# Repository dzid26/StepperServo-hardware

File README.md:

## StepperServoCAN Firmware
https://github.com/dzid26/StepperServoCAN

# StepperServo-hardware
Limits:
- 3.3A peak stall current per phase for 5sec
- 3.3A RMS combined motor continuous current for >1min (i.e. rotating under load but not stalled)
- 32V supply voltage

Features:
- Intended to drive a stepper motor
- High impedance freewheeling with overvoltage protection
- Magnetic angle sensor (can be turned off during sleep)
- CANbus transceiver with standby mode
- Debug port for flashing and configuration with ESD protection
- [Low-side](https://github.com/dzid26/StepperServoCAN/pull/38) current, V_mot and V_Bat, PCB temperature measurements
- Reverse polarity protection and swapped connectors protection; ESD protections on inputs

- Optional Enable port with [Break](https://github.com/dzid26/StepperServoCAN/pull/37) interrupt capability for additional safety
- Optional expansion port for connecting UART/I2C/PWM device or a sensor (0.4A max, or 1A for v0.6)
- Optional solder jumper pads, e.g. for motor identification

## Schematic

## PCB
- single sided PCB for direct mounting on the motor and efficient assembly
- flat bottom allows for heat dissipation and measuring motor temperature

## Motor
Motor tips:
- an examples of motor that produce a lot of torque without needing much gear ratio are Nema23 [104mm](https://www.omc-stepperonline.com/nema-23-bipolar-1-8deg-2-4nm-340oz-in-1-8a-4-95v-57x57x104mm-4-wires-23hs41-1804s) and [56mm](https://www.omc-stepperonline.com/nema-23-bipolar-1-8deg-1-16nm-164-3oz-in-1-5a-5-4v-57x57x56mm-4-wires-23hs22-1504s) - they have dense windings and high torque per amp values
- for space limited applications [this](https://www.aliexpress.com/item/4001349087963.html) coupled with single stage 5:1 gearbox can provide enough torque with relatively low friction and noise from the gearbox. Note: above 2Amps, the torque tapers off and torque ripple becomes apparent!
- rated current should not be exceeded by a lot to avoid torque ripple, motor inefficiency and overheating
- motors with high rated-current (less but thicker winding) can be used to avoid torque ripple problem, provided they are geared enough to generate enough output torque - however large gear ratios can be more prone to backlash and low efficiency which adds to backdrivinility friction
- generally big motors will have smoothest torque and don't need that much gearing

## Angle sensor magnet
- requires diametrically magnetized disk magnet
- Attaching magnet with the glue - [video](https://youtu.be/mQyXR3hITy0?t=41)
- Magnetic field [analysis](/Design/Magnet/README.md) 1-2mm thick and 5-6mm diameter magnets with about 1mm gap can be used

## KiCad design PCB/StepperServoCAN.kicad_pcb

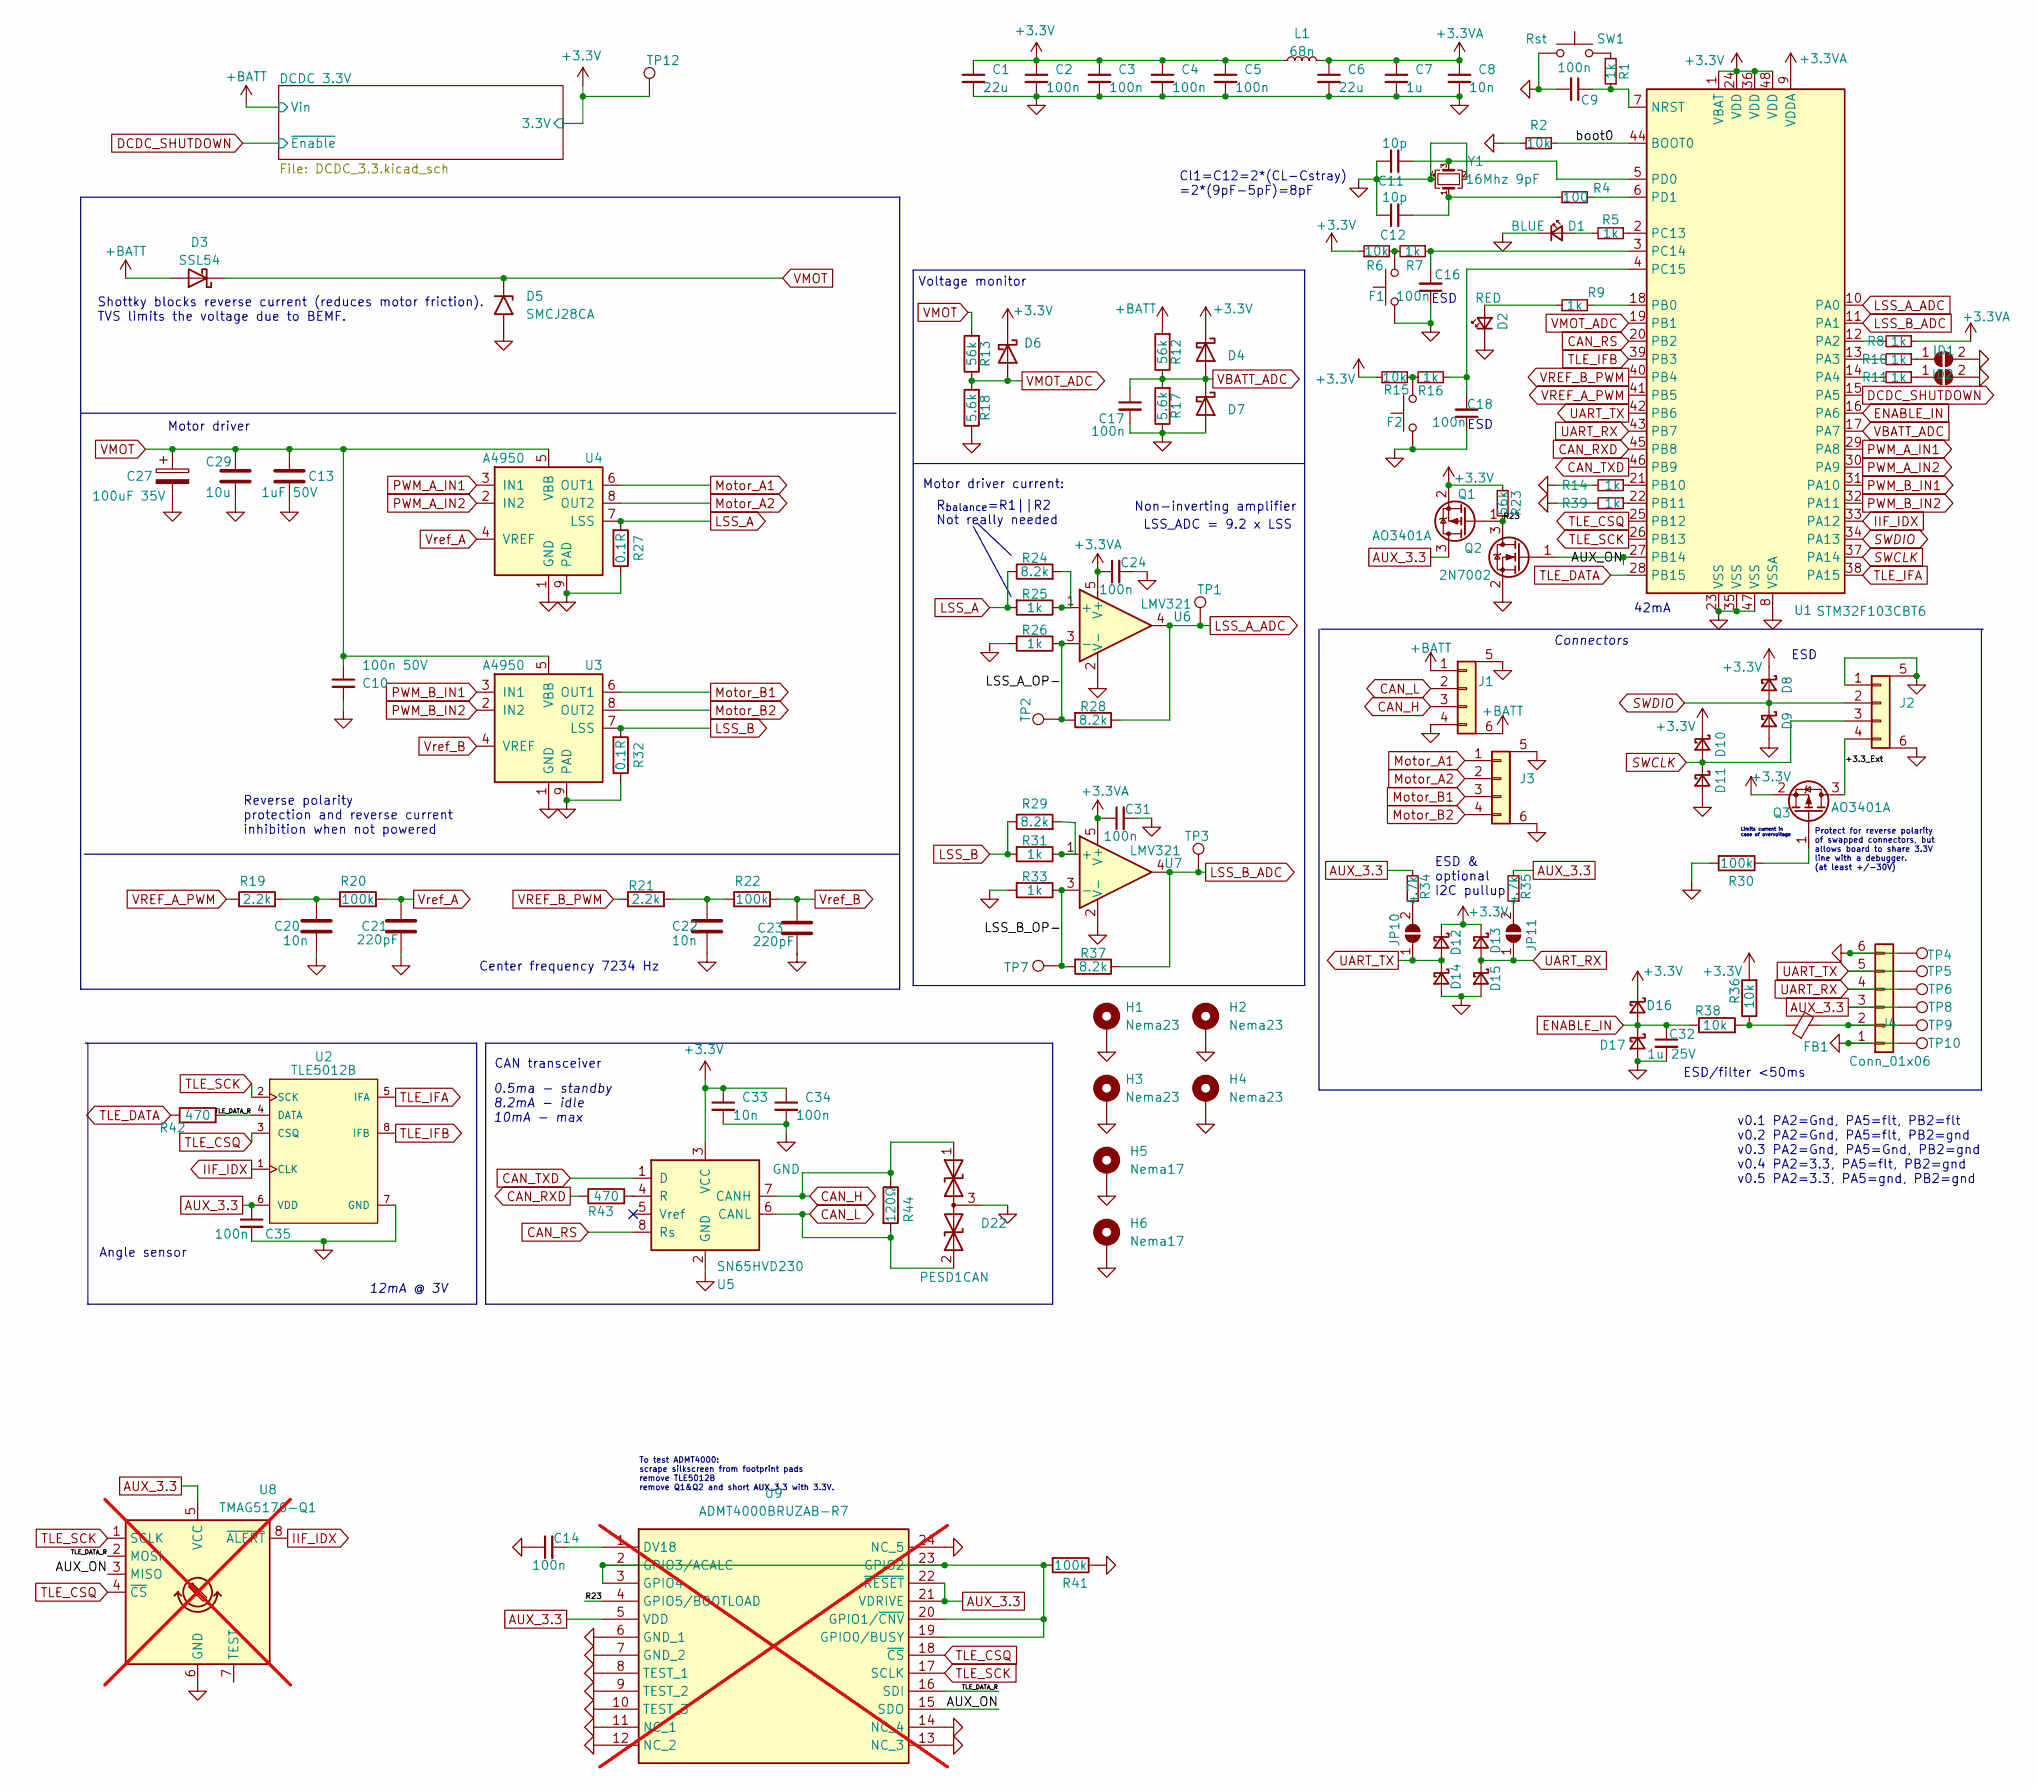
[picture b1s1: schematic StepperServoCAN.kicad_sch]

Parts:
C1, C6: 22u; C_0603_1608Metric; LCSC C59461
C2, C3, C4, C5, C9, C14, C16, C17, C18, C24, C31, C34, C35: 100n; C_0402_1005Metric; LCSC C1525
C7: 1u; C_0402_1005Metric; LCSC C52923
C8, C20, C22, C33: 10n; C_0402_1005Metric; LCSC C15195
C10: 100n 50V; C_0402_1005Metric; LCSC C307331
C11, C12: 10p; C_0402_1005Metric; LCSC C32949
C13: 1uF 50V; C_0805_2012Metric; LCSC C28323
C21, C23: 220pF; C_0402_1005Metric; LCSC C1530
C27: 100uF 35V; CP_Elec_6.3x5.7; LCSC C249982
C29: 10u; C_1206_3216Metric; LCSC C13585
C32: 1u 25V; C_0402_1005Metric; LCSC C52923
D1: BLUE; LED_0603_1608Metric; LCSC C2986058
D2: RED; LED_0603_1608Metric; LCSC C2286
D3: SSL54; D_SMB; LCSC C28646278
D4, D6, D7, D8, D9, D10, D11, D12, D13, D14, D15, D16, D17: 1N5819WS; D_SOD-323; LCSC C191023
D5: SMCJ28CA; D_SMC; LCSC C42371538
D22: PESD1CAN; SOT-23; LCSC C15771
F1, F2: Fcn>; SW_SPST_TL3342; LCSC C318884
FB1: FerriteBead 200mA; L_0603_1608Metric; LCSC C1002
H1, H2, H3, H4: Nema23; MountingHole_3.2mm_M3_ISO14580_Pad_TopOnly
H5, H6: Nema17; MountingHole_3.2mm_M3_ISO14580_Pad_TopOnly; LCSC C2928178
ID1, ID2: Jumper; SolderJumper-2_P1.3mm_Open_TrianglePad1.0x1.5mm
J1: CAR; JST-S4B-XH-SM4-TB; LCSC C54582908
J2: Debug; JST-S4B-XH-SM4-TB; LCSC C54582908
J3: Motor; JST-S4B-XH-SM4-TB; LCSC C54582908
J4: Conn_01x06; TerminalBlock_TE_282834-6_1x06_P2.54mm_Horizontal
JP10, JP11: I2C_PU; SolderJumper-2_P1.3mm_Open_RoundedPad1.0x1.5mm
L1: 68n; L_0603_1608Metric; LCSC C13415
Q1, Q3: AO3401A; SOT-23; LCSC C15127
Q2: 2N7002; SOT-23; LCSC C8545
R1, R5, R7, R8, R9, R10, R11, R14, R16, R25, R26, R31, R33, R39: 1k; R_0402_1005Metric; LCSC C11702
R2, R6, R15, R36, R38: 10k; R_0402_1005Metric; LCSC C25744
R4: 100; R_0402_1005Metric; LCSC C25076
R12, R13, R23: 56k; R_0402_1005Metric; LCSC C25796
R17, R18: 5.6k; R_0402_1005Metric; LCSC C25908
R19, R21: 2.2k; R_0402_1005Metric; LCSC C25879
R20, R22, R30, R41: 100k; R_0402_1005Metric; LCSC C25741
R24, R28, R29, R37: 8.2k; R_0402_1005Metric; LCSC C25924
R27, R32: 0.1R; R_1206_3216Metric_Pad1.30x1.75mm_HandSolder; LCSC C201308
R34, R35: 4.7k; R_0603_1608Metric_Pad0.98x0.95mm_HandSolder; LCSC C23162
R42, R43: 470; R_0603_1608Metric; LCSC C23179
R44: 120Ω; R_1206_3216Metric_Pad1.30x1.75mm_HandSolder; LCSC C17909
SW1: Rst; SW_SPST_TL3342; LCSC C318884
TP1, TP2, TP3, TP7: Pad; TestPoint_Pad_D1.0mm
TP4, TP5, TP6, TP8, TP9, TP10: WirePad; TestPoint_Pad_2.0x2.0mm
TP12: 3.3; TestPoint_Pad_D1.0mm
U1: STM32F103CBT6; LQFP-48_7x7mm_P0.5mm; LCSC C8734
U2: TLE5012B; Infineon-TLE5012-Level_A; LCSC C123083
U3, U4: A4950; SOIC-8-1EP_3.9x4.9mm_P1.27mm_EP2.41x3.3mm_ThermalVias; LCSC C82404
U5: SN65HVD230; SOIC-8_3.9x4.9mm_P1.27mm; LCSC C12084
U6, U7: LMV321; SOT-23-5; LCSC C7972
U8: TMAG5170-Q1; VSSOP-8_3x3mm_P0.65mm; LCSC C5220642; not fitted
U9: ADMT4000BRUZAB-R7; TSSOP-24_4.4x7.8mm_P0.65mm; not fitted
Y1: 16Mhz 9pF; Crystal_SMD_3225-4Pin_3.2x2.5mm; LCSC C13738

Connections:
+3.3V: C1.1, C2.1, C3.1, C4.1, C5.1, C33.1, C34.1, D4.1 (K), D6.1 (K), D8.1 (K), D10.1 (K), D12.1 (K), D13.1 (K), D16.1 (K), L1.1, Q1.2 (S), Q3.2 (S), R6.1, R15.1, R23.2, R36.2, TP12.1 (1_1), U1.1 (VBAT), U1.24 (VDD), U1.36 (VDD), U1.48 (VDD), U5.3 (VCC); also elsewhere on the board
+3.3VA: C6.1, C7.1, C8.1, C24.1, C31.1, L1.2, R8.1, U1.9 (VDDA), U6.5 (V+), U7.5 (V+)
+BATT: D3.2 (A), J1.1, J1.6 (Mount), R12.2; also elsewhere on the board
/+3.3_Ext: J2.4, Q3.3 (D)
/AUX_ON: Q2.1 (G), U1.27 (PB14), U8.3 (MISO), U9.15 (SDO)
/LSS_A_OP-: R26.1, R28.2, TP2.1 (1_1), U6.3 (-)
/LSS_B_OP-: R33.1, R37.2, TP7.1 (1_1), U7.3 (-)
/R23: Q1.1 (G), Q2.3 (D), R23.1, U9.4 (GPIO5/BOOTLOAD)
/TLE_DATA_R: R42.2, U2.4 (DATA), U8.2 (MOSI), U9.16 (SDI)
/boot0: R2.2, U1.44 (BOOT0)
AUX_3.3: C35.1, J4.3, Q1.3 (D), R34.2, R35.2, TP8.1 (1_1), U2.6 (VDD), U8.5 (VCC), U9.5 (VDD), U9.21 (VDRIVE), U9.22 (~RESET)
CAN_H: D22.1 (A1), J1.3, R44.1, U5.7 (CANH)
CAN_L: D22.2 (A2), J1.2, R44.2, U5.6 (CANL)
CAN_RS: U1.20 (PB2), U5.8 (Rs)
CAN_RXD: R43.1, U1.45 (PB8)
CAN_TXD: U1.46 (PB9), U5.1 (D)
DCDC_SHUTDOWN: U1.15 (PA5); also elsewhere on the board
ENABLE_IN: C32.1, D16.2 (A), D17.1 (K), R38.1, U1.16 (PA6)
GND: C1.2, C2.2, C3.2, C4.2, C5.2, C6.2, C7.2, C8.2, C9.2, C10.2, C11.1, C12.1, C13.2, C14.1, C16.1, C17.2, C18.1, C20.2, C21.2, C22.2, C23.2, C24.2, C27.2, C29.2, C31.2, C32.2, C33.2, C34.2, C35.2, D1.1 (K), D2.1 (K), D5.2 (A2), D7.2 (A), D9.2 (A), D11.2 (A), D14.2 (A), D15.2 (A), D17.2 (A), D22.3 (common), F1.2, F2.2, H1.1 (1_1), H2.1 (1_1), H3.1 (1_1), H4.1 (1_1), H5.1 (1_1), H6.1 (1_1), ID1.2 (B), ID2.2 (B), J1.4, J1.5 (Mount), J2.1, J2.5 (Mount), J2.6 (Mount), J3.5 (Mount), J3.6 (Mount), J4.1, J4.6, Q2.2 (S), R2.1, R14.2, R17.1, R18.1, R26.2, R27.1, R30.2, R32.1, R33.2, R39.2, R41.1, SW1.1, TP4.1 (1_1), TP10.1 (1_1), U1.8 (VSSA), U1.23 (VSS), U1.35 (VSS), U1.47 (VSS), U2.7 (GND), U3.1 (GND), U3.9 (PAD), U4.1 (GND), U4.9 (PAD), U5.2 (GND), U6.2 (V-), U7.2 (V-), U8.6 (GND), U9.6 (GND_1), U9.7 (GND_2), U9.8 (TEST_1), U9.9 (TEST_2), U9.10 (TEST_3), U9.11 (NC_1), U9.12 (NC_2), U9.13 (NC_3), U9.14 (NC_4), U9.24 (NC_5), Y1.2, Y1.4; also elsewhere on the board
IIF_IDX: U1.33 (PA12), U2.1 (CLK), U8.8 (~ALERT)
LSS_A: R24.1, R25.2, R27.2, U4.7 (LSS)
LSS_A_ADC: R28.1, TP1.1 (1_1), U1.10 (PA0), U6.4
LSS_B: R29.1, R31.2, R32.2, U3.7 (LSS)
LSS_B_ADC: R37.1, TP3.1 (1_1), U1.11 (PA1), U7.4
Motor_A1: J3.1, U4.6 (OUT1)
Motor_A2: J3.2, U4.8 (OUT2)
Motor_B1: J3.3, U3.6 (OUT1)
Motor_B2: J3.4, U3.8 (OUT2)
unnamed: C12.2, R4.1, Y1.1
unnamed: C20.1, R19.2, R20.1
unnamed: C22.1, R21.2, R22.1
unnamed: D1.2 (A), R5.2
unnamed: D2.2 (A), R9.1
unnamed: F1.1, R6.2, R7.2
unnamed: F2.1, R15.2, R16.1
unnamed: FB1.1, R36.1, R38.2
unnamed: ID1.1 (A), R10.1
unnamed: ID2.1 (A), R11.1
unnamed: FB1.2, J4.2, TP9.1 (1_1)
unnamed: JP10.2 (B), R34.1
unnamed: JP11.2 (B), R35.1
unnamed: Q3.1 (G), R30.1
unnamed: R1.2, SW1.2
unnamed: C9.1, R1.1, U1.7 (NRST)
unnamed: R8.2, U1.12 (PA2)
unnamed: R10.2, U1.13 (PA3)
unnamed: R11.2, U1.14 (PA4)
unnamed: R9.2, U1.18 (PB0)
unnamed: R14.1, U1.21 (PB10)
unnamed: R39.1, U1.22 (PB11)
unnamed: R5.1, U1.2 (PC13)
unnamed: C16.2, R7.1, U1.3 (PC14)
unnamed: C18.2, R16.2, U1.4 (PC15)
unnamed: C11.2, U1.5 (PD0), Y1.3
unnamed: R4.2, U1.6 (PD1)
unnamed: R43.2, U5.4 (R)
unnamed: R24.2, R25.1, U6.1 (+)
unnamed: R29.2, R31.1, U7.1 (+)
unnamed: C14.2, U9.1 (DV18)
unnamed: R41.2, U9.2 (GPIO3/ACALC), U9.3 (GPIO4), U9.19 (GPIO0/BUSY), U9.20 (GPIO1/~CNV), U9.23 (GPIO2)
PWM_A_IN1: U1.29 (PA8), U4.3 (IN1)
PWM_A_IN2: U1.30 (PA9), U4.2 (IN2)
PWM_B_IN1: U1.31 (PA10), U3.3 (IN1)
PWM_B_IN2: U1.32 (PA11), U3.2 (IN2)
SWCLK: D10.2 (A), D11.1 (K), J2.3, U1.37 (PA14)
SWDIO: D8.2 (A), D9.1 (K), J2.2, U1.34 (PA13)
TLE_CSQ: U1.25 (PB12), U2.3 (CSQ), U8.4 (~CS), U9.18 (~CS)
TLE_DATA: R42.1, U1.28 (PB15)
TLE_IFA: U1.38 (PA15), U2.5 (IFA)
TLE_IFB: U1.39 (PB3), U2.8 (IFB)
TLE_SCK: U1.26 (PB13), U2.2 (SCK), U8.1 (SCLK), U9.17 (SCLK)
UART_RX: D13.2 (A), D15.1 (K), J4.4, JP11.1 (A), TP6.1 (1_1), U1.43 (PB7)
UART_TX: D12.2 (A), D14.1 (K), J4.5, JP10.1 (A), TP5.1 (1_1), U1.42 (PB6)
VBATT_ADC: C17.1, D4.2 (A), D7.1 (K), R12.1, R17.2, U1.17 (PA7)
VMOT: C10.1, C13.1, C27.1, C29.1, D3.1 (K), D5.1 (A1), R13.2, U3.5 (VBB), U4.5 (VBB)
VMOT_ADC: D6.2 (A), R13.1, R18.2, U1.19 (PB1)
VREF_A_PWM: R19.1, U1.41 (PB5)
VREF_B_PWM: R21.1, U1.40 (PB4)
Vref_A: C21.1, R20.2, U4.4 (VREF)
Vref_B: C23.1, R22.2, U3.4 (VREF)

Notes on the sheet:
LSS_ADC = 9.2 x LSS
42mA
ESD & optional I2C pullup
R_{balance}=R1||R2 Not really needed
v0.1 PA2=Gnd, PA5=flt, PB2=flt v0.2 PA2=Gnd, PA5=flt, PB2=gnd v0.3 PA2=Gnd, PA5=Gnd, PB2=gnd v0.4 PA2=3.3, PA5=flt, PB2=gnd v0.5 PA2=3.3, PA5=gnd, PB2=gnd
CAN transceiver
Non-inverting amplifier
Center frequency 7234 Hz
Angle sensor
Protect for reverse polarity of swapped connectors, but allows board to share 3.3V line with a debugger. (at least +/-30V)
ESD
Motor driver
ESD/filter <50ms
Shottky blocks reverse current (reduces motor friction). TVS limits the voltage due to BEMF.
To test ADMT4000: scrape silkscreen from footprint pads remove TLE5012B remove Q1&Q2 and short AUX_3.3 with 3.3V.
Limits current in case of overvoltage
Connectors
12mA @ 3V
Reverse polarity protection and reverse current inhibition when not powered
Voltage monitor
0.5ma - standby 8.2mA - idle 10mA - max
Cl1=C12=2*(CL-Cstray) =2*(9pF-5pF)=8pF
Motor driver current:

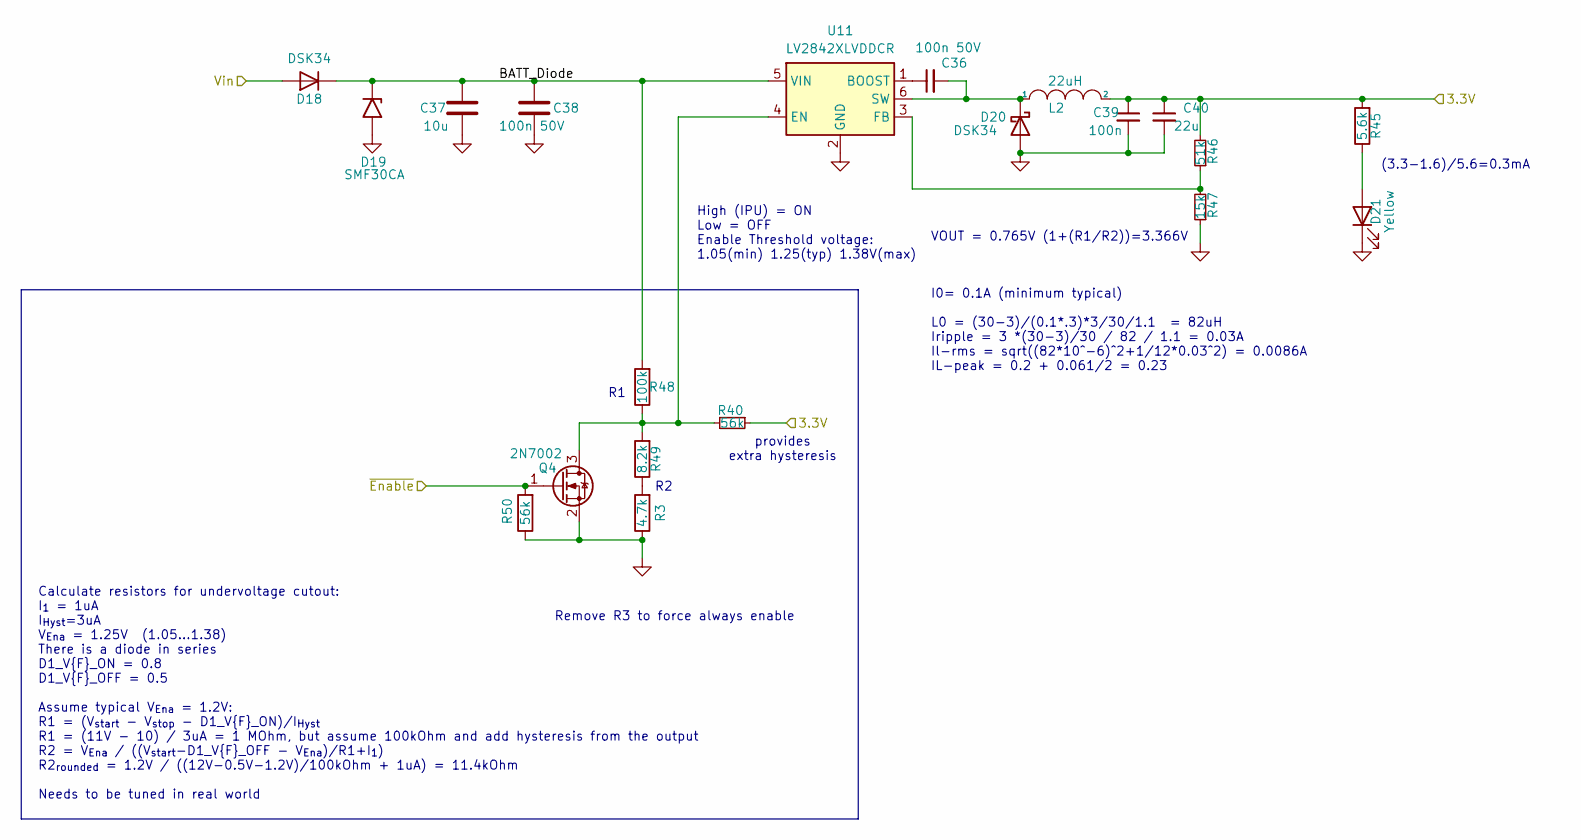
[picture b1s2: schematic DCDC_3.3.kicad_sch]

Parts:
C36, C38: 100n 50V; C_0402_1005Metric; LCSC C307331
C37: 10u; C_0805_2012Metric; LCSC C440198
C39: 100n; C_0402_1005Metric; LCSC C1525
C40: 22u; C_0603_1608Metric; LCSC C59461
D18, D20: DSK34; D_SOD-123F; LCSC C7502709
D19: SMF30CA; D_SMF; LCSC C19077519
D21: Yellow; LED_0603_1608Metric; LCSC C89811
L2: 22uH; L_Changjiang_FTC252010S; LCSC C5832391
Q4: 2N7002; SOT-23; LCSC C8545
R3: 4.7k; R_0402_1005Metric; LCSC C25900
R40, R50: 56k; R_0402_1005Metric; LCSC C25796
R45: 5.6k; R_0402_1005Metric; LCSC C25908
R46: 51k; R_0402_1005Metric; LCSC C25794
R47: 15k; R_0402_1005Metric; LCSC C25756
R48: 100k; R_0402_1005Metric; LCSC C25741
R49: 8.2k; R_0402_1005Metric; LCSC C25924
U11: LV2842XLVDDCR; TSOT-23-6; LCSC C225807

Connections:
+3.3V: C39.1, C40.1, L2.2, R40.1, R45.2, R46.2; also elsewhere on the board
+BATT: D18.2 (A); also elsewhere on the board
/DCDC 3.3V/BATT_Diode: C37.1, C38.1, D18.1 (K), D19.1 (A1), R48.2, U11.5 (VIN)
DCDC_SHUTDOWN: Q4.1 (G), R50.2; also elsewhere on the board
GND: C37.2, C38.2, C39.2, C40.2, D19.2 (A2), D20.2 (A), D21.1 (K), Q4.2 (S), R3.1, R47.1, R50.1, U11.2 (GND); also elsewhere on the board
unnamed: C36.2, D20.1 (K), L2.1, U11.6 (SW)
unnamed: D21.2 (A), R45.1
unnamed: Q4.3 (D), R40.2, R48.1, R49.2, U11.4 (EN)
unnamed: R3.2, R49.1
unnamed: C36.1, U11.1 (BOOST)
unnamed: R46.1, R47.2, U11.3 (FB)

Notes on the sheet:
provides extra hysteresis
(3.3-1.6)/5.6=0.3mA
Calculate resistors for undervoltage cutout: I_{1} = 1uA I_{Hyst}=3uA V_{Ena} = 1.25V (1.05...1.38) There is a diode in series D1_V{F}_ON = 0.8 D1_V{F}_OFF = 0.5 Assume typical V_{Ena} = 1.2V: R1 = (V_{start} - V_{stop} - D1_V{F}_ON)/I_{Hyst} R1 = (11V - 10) / 3uA = 1 MOhm, but assume 100kOhm and a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
I0= 0.1A (minimum typical) L0 = (30-3)/(0.1*.3)*3/30/1.1 = 82uH Iripple = 3 *(30-3)/30 / 82 / 1.1 = 0.03A Il-rms = sqrt((82*10^-6)^2+1/12*0.03^2) = 0.0086A IL-peak = 0.2 + 0.061/2 = 0.23
Remove R3 to force always enable
High (IPU) = ON Low = OFF Enable Threshold voltage: 1.05(min) 1.25(typ) 1.38V(max)
VOUT = 0.765V (1+(R1/R2))=3.366V

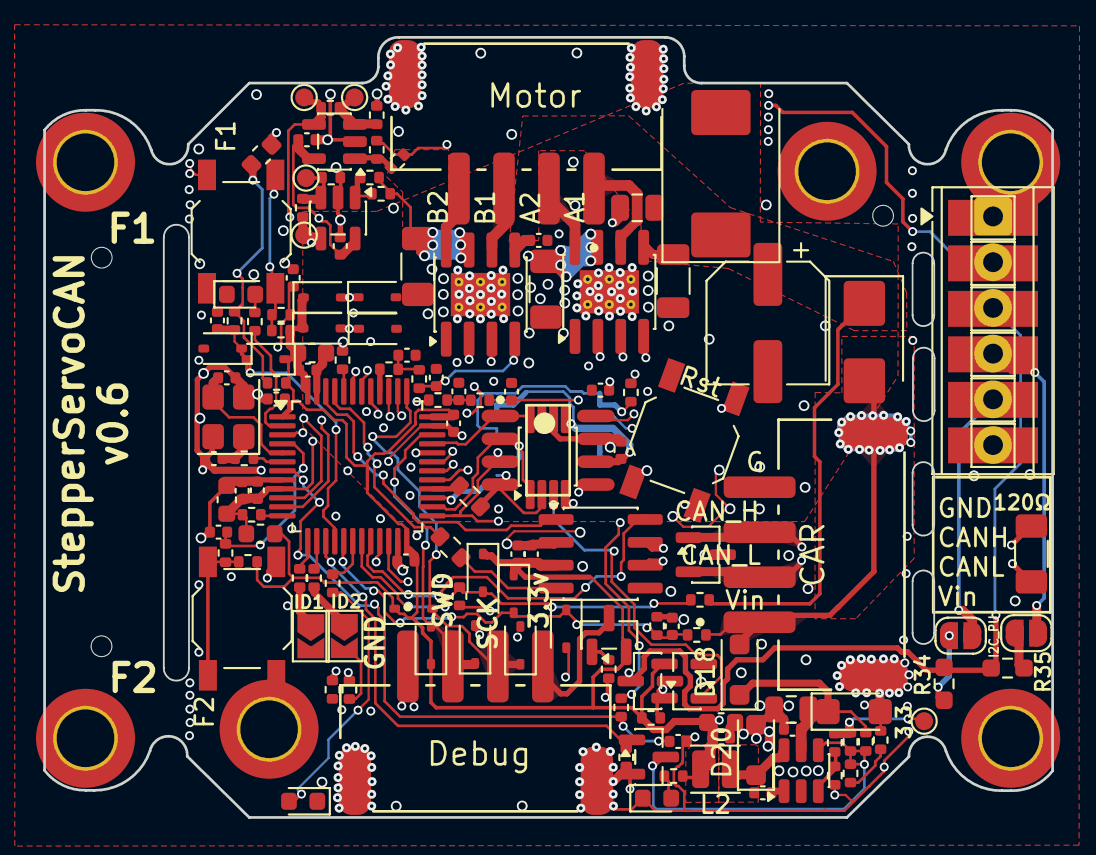
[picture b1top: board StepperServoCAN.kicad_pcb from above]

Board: 4 copper layers, 56.0 x 43.3 mm, 152 parts (1 on the bottom side), 87 nets.

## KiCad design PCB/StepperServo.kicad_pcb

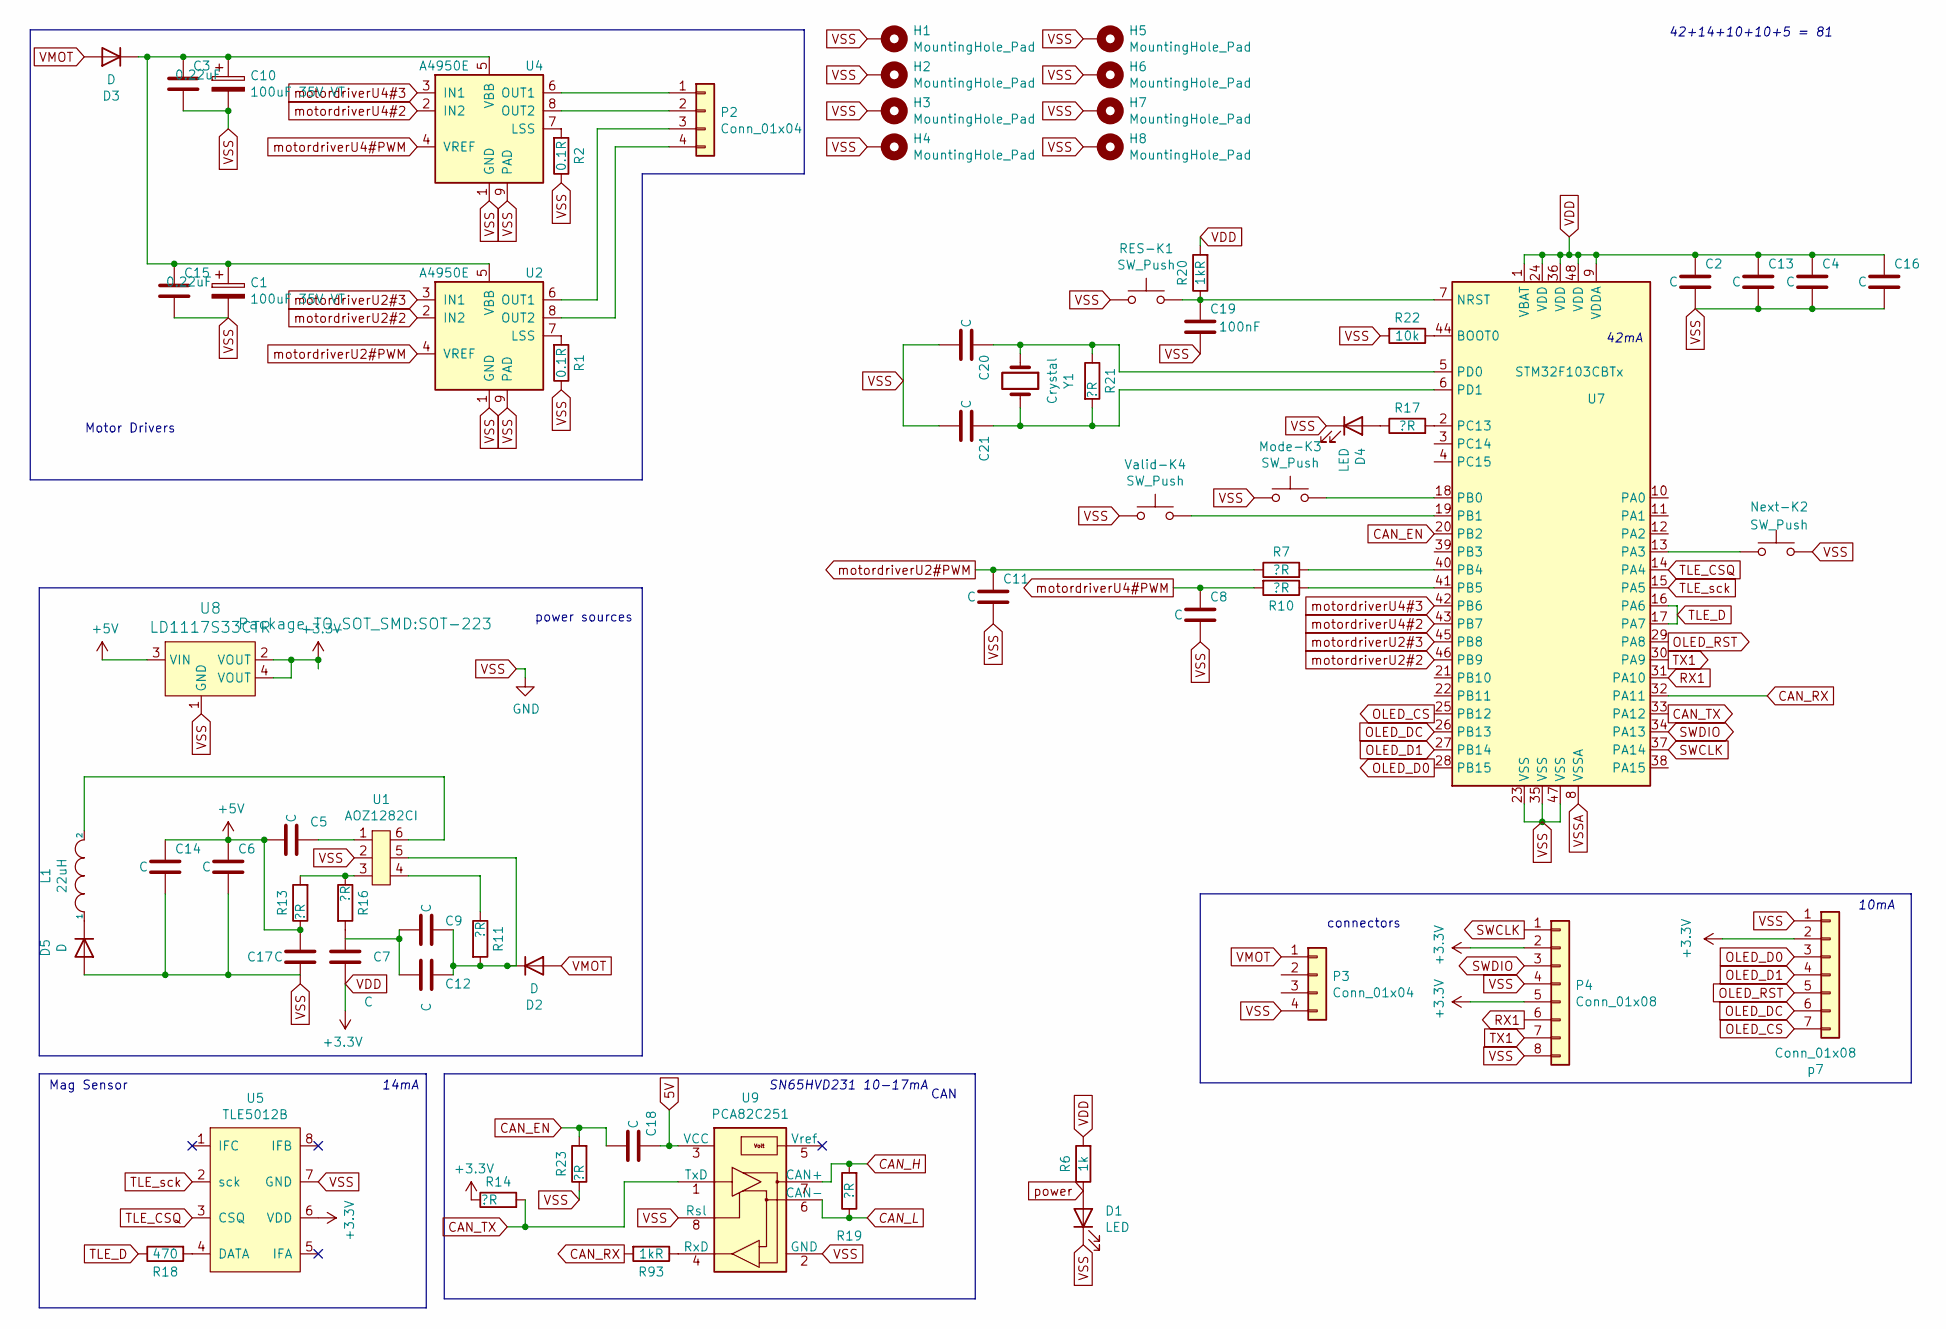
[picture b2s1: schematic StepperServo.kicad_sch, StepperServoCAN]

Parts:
C1, C10: 100uF 35V VT; CP_Elec_6.3x7.7
C2, C4, C5, C8, C11, C12, C13, C14, C16, C18, C20, C21: C; C_0603_1608Metric
C3, C15: 0.22uF; C_0805_2012Metric
C6, C7, C9, C17: C; C_0805_2012Metric
C19: 100nF; C_0603_1608Metric
D1, D4: LED; LED_0603_1608Metric
D2, D3, D5: D; D_2512_6332Metric
H1, H2, H3, H4, H5, H6, H7, H8: MountingHole_Pad; MountingHole_2.7mm_M2.5_ISO14580_Pad_TopBottom
L1: 22uH; L_Wuerth_MAPI-4030
Mode-K3: SW_Push; SW_SPST_TL3342
Next-K2: SW_Push; SW_SPST_TL3342
P2, P3: Conn_01x04; JST_XH_B4B-XH-A_1x04_P2.50mm_Vertical
P4: Conn_01x08; PinHeader_1x08_P2.54mm_Vertical
R1, R2: 0.1R; R_2512_6332Metric
R6: 1k; R_0603_1608Metric
R7, R10, R11, R13, R14, R16, R17, R21, R23: ?R; R_0603_1608Metric
R18: 470; R_0805_2012Metric
R19: ?R; R_1206_3216Metric
R20, R93: 1kR; R_0603_1608Metric
R22: 10k; R_0603_1608Metric
RES-K1: SW_Push; SW_SPST_TL3342
U1: AOZ1282CI; SOT-23-6
U2, U4: A4950E; SOIC-8-1EP_3.9x4.9mm_P1.27mm_EP2.41x3.3mm
U5: TLE5012B; Infineon_PG-DSO-8-27_3.9x4.9mm_EP2.65x3mm
U7: STM32F103CBTx; LQFP-48_7x7mm_P0.5mm
U8: LD1117S33CTR; SOT-223; MPN LD1117S33CTR; Digi-Key_PN 497-1241-1-ND
U9: PCA82C251; SO-8_3.9x4.9mm_P1.27mm
Valid-K4: SW_Push; SW_SPST_TL3342
Y1: Crystal; Crystal_SMD_EuroQuartz_MT-4Pin_3.2x2.5mm_HandSoldering
p7: Conn_01x08; PinSocket_1x07_P2.54mm_Vertical

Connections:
5V: C18.1, U9.3 (VCC)
+5V: C5.2, C6.1, C14.1, C17.1, R13.1, U8.3 (VIN)
CAN_EN: C18.2, R23.2, U7.20 (PB2)
CAN_RX: R93.2, U7.32 (PA11)
CAN_TX: R14.2, U7.33 (PA12), U9.1 (TxD)
unnamed: C1.1, C3.1, C10.1, C15.1, D3.1 (K), U2.5 (VBB), U4.5 (VBB)
unnamed: C5.1, U1.1
unnamed: C7.1, R16.2
unnamed: C9.1, C12.1, D2.1 (K), R11.2, U1.5
unnamed: C9.2, C12.2
unnamed: C6.2, C14.2, D5.2 (A)
unnamed: C19.1, R20.1, RES-K1.2, U7.7 (NRST)
unnamed: C20.1, R21.1, U7.5 (PD0), Y1.1
unnamed: C21.1, R21.2, U7.6 (PD1), Y1.2
unnamed: D4.2 (A), R17.1
unnamed: D5.1 (K), L1.1
unnamed: L1.2, U1.6
unnamed: Mode-K3.2, U7.18 (PB0)
unnamed: Next-K2.1, U7.13 (PA3)
unnamed: P2.1, U4.6 (OUT1)
unnamed: P2.2, U4.8 (OUT2)
unnamed: P2.3, U2.6 (OUT1)
unnamed: P2.4, U2.8 (OUT2)
unnamed 23: R19.1, U9.6 (CAN-); also elsewhere on the board
unnamed 24: R19.2, U9.7 (CAN+); also elsewhere on the board
unnamed: R1.2, U2.7 (LSS)
unnamed: R2.2, U4.7 (LSS)
unnamed: R7.2, U7.40 (PB4)
unnamed: R10.1, U7.41 (PB5)
unnamed: R11.1, U1.4
unnamed: R13.2, R16.1, U1.3
unnamed: R17.2, U7.2 (PC13)
unnamed: R18.2, U5.4 (DATA)
unnamed: R22.1, U7.44 (BOOT0)
unnamed: R93.1, U9.4 (RxD)
unnamed: U7.19 (PB1), Valid-K4.2
OLED_CS: U7.25 (PB12), p7.7
OLED_D0: U7.28 (PB15), p7.3
OLED_D1: U7.27 (PB14), p7.4
OLED_DC: U7.26 (PB13), p7.6
OLED_RST: U7.29 (PA8), p7.5
RX1: P4.6, U7.31 (PA10)
SWCLK: P4.1, U7.37 (PA14)
SWDIO: P4.3, U7.34 (PA13)
TLE_CSQ: U5.3 (CSQ), U7.14 (PA4)
TLE_D: R18.1, U7.16 (PA6), U7.17 (PA7)
TLE_sck: U5.2 (sck), U7.15 (PA5)
TX1: P4.7, U7.30 (PA9)
VDD: C2.1, C4.1, C7.2, C13.1, C16.1, P4.2, P4.5, R6.2, R14.1, R20.2, U5.6 (VDD), U7.1 (VBAT), U7.9 (VDDA), U7.24 (VDD), U7.36 (VDD), U7.48 (VDD), U8.2 (VOUT), U8.4 (VOUT), p7.2
VMOT: D2.2 (A), D3.2 (A), P3.1; also elsewhere on the board
VSS: C1.2, C2.2, C3.2, C4.2, C8.2, C10.2, C11.2, C13.2, C15.2, C16.2, C17.2, C19.2, C20.2, C21.2, D1.1 (K), D4.1 (K), H1.1, H2.1, H3.1, H4.1, H5.1, H6.1, H7.1, H8.1, Mode-K3.1, Next-K2.2, P3.4, P4.4, P4.8, R1.1, R2.1, R22.2, R23.1, RES-K1.1, U1.2, U2.1 (GND), U2.9 (PAD), U4.1 (GND), U4.9 (PAD), U5.7 (GND), U7.23 (VSS), U7.35 (VSS), U7.47 (VSS), U8.1 (GND), U9.2 (GND), U9.8 (Rsl), Valid-K4.1, p7.1; also elsewhere on the board
VSSA: U7.8 (VSSA)
motordriverU2#2: U2.2 (IN2), U7.46 (PB9)
motordriverU2#3: U2.3 (IN1), U7.45 (PB8)
motordriverU2#PWM: C11.1, R7.1, U2.4 (VREF)
motordriverU4#2: U4.2 (IN2), U7.43 (PB7)
motordriverU4#3: U4.3 (IN1), U7.42 (PB6)
motordriverU4#PWM: C8.1, R10.2, U4.4 (VREF)
power: D1.2 (A), R6.1

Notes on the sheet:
CAN
42mA
10mA
connectors
Motor Drivers
42+14+10+10+5 = 81
SN65HVD231 10-17mA
Mag Sensor
power sources
14mA

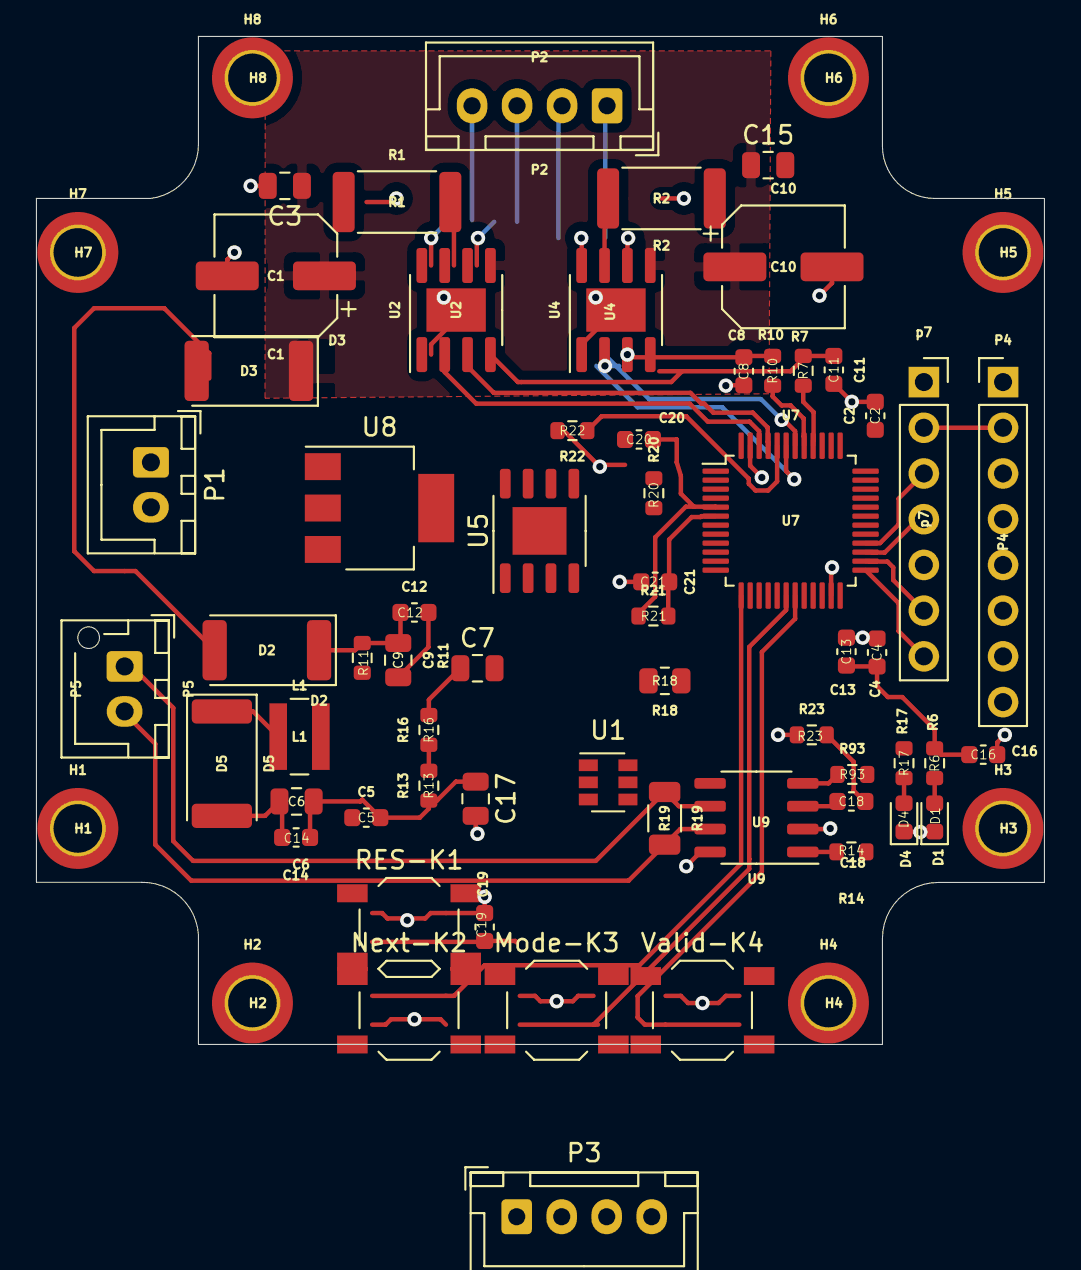
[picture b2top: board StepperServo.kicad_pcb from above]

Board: 2 copper layers, 56.0 x 56.0 mm, 70 parts (1 on the bottom side), 58 nets.

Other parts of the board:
P1: Conn_01x06; JST_XH_B2B-XH-A_1x02_P2.50mm_Vertical
P5: Conn_01x02; JST_XH_B2B-XH-AM_1x02_P2.50mm_Vertical

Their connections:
unnamed 23: P5.1; also elsewhere on the board
unnamed 24: P5.2; also elsewhere on the board
VMOT: P1.2; also elsewhere on the board
VSS: P1.1; also elsewhere on the board

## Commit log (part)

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2022-08-21 Added misssing footprints to pcb
2022-08-21 Removed dir, step, enable
2022-08-21 Added picture
2022-08-21 Added datasheets
2022-08-21 Files base name - StepperServo. Based on Intellistep.
2022-08-21 Removed dip switches
2022-08-22 Boot0 to gnd
2022-08-26 NRST pull'up most likely not needed - set to virtual. A bit of cleanup.
2022-08-27 Kicad 6
2022-08-27 Added attribution
2022-09-18 Clean
2022-09-18 Tips
2022-09-18 datasheets
2022-09-18 TLE5012 library
2022-09-19 Removed local settings file
2022-09-19 Dummy CAN enable line not connected in s42b
2022-09-19 S42B uses single supply diode and 5V and 3.3V lines are active when back-driving
2022-09-21 Created project and schematic
2022-09-21 Low side simple ADC
2022-09-21 Revised capacitor package sizes due to DC bias. Added VDD decoupling capacitors and VDDA filter.
2022-09-21 Reduced capacitor bom
2022-09-21 Removed rescue artifacts
2022-09-22 LM317 reverse diode
2022-09-22 Added Vmot protection
2022-09-22 Resistor footprints
2022-09-23 Initial layout. Footprints fixes.
2022-09-23 Debug port wrong insertion protection. LM317 adj pin filtering.
2022-09-23 Added mounting Nema17 holes and Nema23 outline
2022-09-27 Routing
2022-09-27 Components positioning and routing
2022-09-27 Added P-Mosfet reverse polarity protection for the motor
2022-09-27 Added jlcpcb fab contraints
2022-09-27 Repositioned TLE5012B SPI pins.
2022-09-29 Fixed fottprint ids. Routing. V-cut on edge layer. DRC exclusions
2022-09-29 OP-amp reconfigured to non-inverting amplification with compensation resistor and 9.2 gain to avoid clipping
2022-09-30 Untented thermal vias. Added DCDC footprints.
2022-10-01 DCDC power. . Analog +3.3 netrouted to op amps. Added backup power. Added test vias and spare caps.
2022-10-01 Rotated button
2022-10-02 Added CAN RXD current limiting resistor for sleep state.
2022-10-02 Routing cleanup DRC
2022-10-02 Geographical reannotate
2022-10-04 Zenner diode to protect gate of reverse polarity mosfets. Extra DCDC caps.
2022-10-05 3.3v DCDC. Bigger coil for small currents. Removed LDO. Rearranged. Optimized power traces widths.
2022-10-05 10uF 0402 decoupling -> 22uF 0603. Optimized track widths
2022-10-12 Mosfet bemf overvoltage protection. Solder jumpers, extra LED. Mov ed analog inputs. DRC.
2022-10-12 VMOT_ADC - removed protection zener and 2x resolution on voltage divider.
2022-10-13 Moved jst footprint anchor. Removed second shunts from bom. Refreshed nets.
2022-10-14 Labels cleanup.
2022-10-16 Removed old files
2022-11-12 Removed extra test components. Mosfet closer together.
2022-11-12 Added shaft magnet FEM analysis
2022-11-29 Swapped red/blue LED. Rearranged related tracks.
2022-12-08 Filled copper around A4950 for better thermals
2022-12-16 Added temporary pictures from discord and guidlines.
2022-12-17 Moved JST connector reference point so that actual connector sticks out more after manufacturing
2022-12-17 clean nets
2022-12-17 Text
2022-12-18 Connected TLE_IFA and TLE_IFB pins from angle sensor. Optimized routings
2022-12-18 Added second button
2022-12-18 Removed small elements silk screen designators. Cleaned up vias
2022-12-18 Spaced out motor drivers
2022-12-19 Moved magnet inspection coutout for possibly better visibility
2022-12-20 Denser LSS_B opamp
2022-12-20 Removed thermal relief from shunt resistors for heat dissipation and from connector anchors to be stronger
2023-01-02 Mosfets replaced with Shottky and TVS.
2023-01-04 Added copper under DCDC inductor and diode for better heat transfer in case of 3.3v short
2023-01-04 Back to thinner V_bat trace for better EMI
2023-01-21 Steeper 2nd order filter for PWM DAC.
2023-01-21 Larger A4950 V_mot bypas caps
2023-01-21 Added separate V_BATT ADC
2023-01-22 Made some space near button 1
2023-01-23 Added Enable/break pin with a filter. Repinned motor driver to Tim1.
2023-01-23 Debug port ESD protection
2023-01-24 RC filter ESD protection on buttons
2023-01-24 Added pull up on button RC filter for quicker charge on startup
2023-01-25 Pulled down unused pins. Added UART pads just in case
2023-01-25 Opamp testpoint
2023-01-25 Routed TLE_IFC to spare pin
2023-01-27 Fixed part numbers
2023-01-27 Enlarged exposed ground. Silkscreen fixes.
2023-01-29 Updated graphics
2023-03-19 Corrected max current text
2023-06-10 Kicad 7
2023-06-10 JST connector - rounded pads
2023-06-10 JST connector - narrower lead pads by 0.1mm
2023-06-10 JST connector - mounting pads closer together by 0.1mm each
2023-06-10 JST connector - shorter lead pads by 0.5mm
2023-06-10 JST connector - rounded more for self alligning effect
2023-06-10 JST connector - mounting pads closer together by another 0.1mm each, and truncated by 0.1mm from above
2023-06-10 JST connector - PCB updated and reflowd
2023-06-10 Stronger big cap pad
2023-06-12 Relocated optional enable connector to the right
2023-06-13 DRC Through hole to smd settings
2023-06-13 Removed sense resitor 2512 spare footprint. Board widened by 0.4mm
2023-06-13 Updated footprints from kicad library (rounded pads). Added more small vias for the fets. DRC fixes
2023-06-13 Power lines thickness
2023-06-13 Replaced 0.2mm tracks with 0.15mm. Removed rx/tx testpoints
2023-06-14 Added solder jumper for CAN terminator resistor
2023-06-14 Added overvoltage protection to Vmot adc
2023-06-14 Added VBATT_ADC protection agains large negative and positive voltages
2023-06-14 Power LED relocated to the edge
2023-06-15 Tighter bottom layer routing
2023-06-15 Added back 3d model for A4950
2023-06-15 Updated inductor footprint
2023-06-15 DCDC 30V TVS extra protection. Enable pin TVS on the MCU side.
2023-06-21 Brighter RED LED
2023-06-22 Removed CAN Rs resistor. Rotated terminator resistor.
2023-06-23 Reset switch oriented vertically
2023-06-24 TLE5012B powered conditionally
2023-06-24 Added more powerfull CAN terminator resistor. Uses handsolder pad.
2023-06-24 Bigger decoupling cap vias
2023-06-25 Seperated A4950 and lifted. LSS vias.
2023-06-25 Packed DC-DC into a subsystem/ Added tap points to opamps
2023-06-27 New DC/DC with efficient low current mode. Higher switch freq - smaller footprint.
2023-06-28 More copper on VBAT
2023-06-28 4 layer PCB. Routing optimizations on top layer. Inner layers are plane grounds for better thermals and also EMI.
2023-06-29 Added Vgs protection for debug port reverse polarity protection mosfet.
2023-06-29 Stronger reverse polarity protection mosfet
2023-06-29 Removed back zener from reverse polarity mosfet as it's not needed.
2023-06-29 Added load switching mosfet for TLE5012b
2023-06-29 Thermal vias on TVS pad
2023-06-30 P-channel aux load switching pullup (normally opened). Optional disabling of DCDC
2023-07-01 Smaller Thermal vias. Returned to slder mask in the back.
2023-07-03 Inverted bottom silkscreen to make bottom even for better heat conductivity.
2023-07-06 Mosfets for load switchiong. DCDC Enable pin. Rerouting.
2023-07-06 Wake on low power HAL
2023-07-06 DCDC force enable option
2023-07-06 Added jumper for the DCDC enable line
2023-07-06 Added undervoltage shutdown filter
2023-07-07 JLC actions
2023-07-07 Added test footprint for low power TMAG5170 sensor
2023-07-07 Added UART/I2C aux connector
2023-07-08 Optimized break in filter
2023-07-08 Removed ground loop due to LSS_A for 2 layer board
2023-07-08 Bigger cap for B phase driver
2023-07-08 Crystal small ground guard ring
2023-07-08 Lots of thermal vias. Resistors radiator.
2023-07-08 Spare 1pF caps
2023-07-09 1.2mm board. Wider snap tabs
2023-07-10 Minor prod cleanup
2023-07-10 Improved spacing for the fab. Adjusted connectors anchor 0.2mm outward
2023-07-12 Fab not happy with long slots
2023-07-13 Fab not heappy with spacing. 1N5819WS is fat.
2023-07-13 Added SWO tap point
2023-07-13 Aux origin
2023-08-04 v0.2 Update README.md
2023-08-04 Removed spare caps
2023-08-20 Debug connector labels
2023-09-27 Removed test LDO regulator
2023-09-27 Moved experimental wakeup hal sensor close to the center
2023-09-27 Relocated 3.3 load switches
2023-09-28 CAN tranciever moved to the left slightly, to make more space if someone needs to remove the terminator resistor.
2023-09-29 Direct ground path from sense resistor to electrolitic capacitor. Aux 3.3 path optimized.
2023-10-11 Added 3.3v tap point.
2023-10-11 Fixed 3d model links for an export Added spare driver chip pads.
2023-10-11 Versioning. Connectors center pos for fab.
2024-08-24 Using low-rds on AT8236
2024-11-17 Kicad8. Also clear zone filling before saving
2024-11-17 Kicad 8 - updated PCB from schematic.
2024-11-19 removed hal test circuit and spare soic-8
2024-11-19 removed vmot adc filtering cap
2024-11-19 More powerful and lower breakdown voltage SMCJ28CA TVS. Better component placement - more ground pour. Capacitors moved away from mounting hole to avoid cracking
2024-11-19 reenable teardrops, and some routing
2024-11-20 Nema23 holes follow StepperOnline dimensions
2024-11-20 Thermal reliefs for JST connectors to avoid creep. Added via stitching to reinforce pads.
2024-11-20 relocated termination resistor for easy access
2024-11-20 PESD1CAN esd protection
2024-12-09 Larger pads for DCDC inductor for better thermal dissipation when shorted etc. Outline cleanup.
2024-12-09 added exclusions again after e01c75586d4075f4e024597e5ee9bc4a665d9208
2024-12-12 ability to fully shutdown on low voltage. Power back on above 11V.
2024-12-12 Larger thermal vias
2024-12-12 Reverted AT8236 back to A4950 for better current control capabilities
2024-12-13 Moved some signals to inner layer to free up top ground for better thermals
2024-12-15 thicker uart esd trace
2024-12-15 nicer edge cuts
2024-12-15 kicad 8 sot-23
2024-12-20 Moved experimental TLE_IF (encoder) interface to dedicated channel 2 of tim2
2024-12-20 cleanup, silk
2024-12-21 Re-annotated ICs
2024-12-21 Added ADMT4000 test footprint
2024-12-21 tooling holes
2024-12-21 0.865mm prepeg
2024-12-21 Removed dead properties. Found alternative Parts D1, D22, R27. PEDSCAN uses SOT323-3 footprint now
2024-12-21 Revert "0.865mm prepeg" Back to 0.2104 due to cost. This reverts commit 9494b9fe4c37bd1a66a87f1883a1c5a6efe1d1f9.
2024-12-21 1oz inner layer for better thermals
2025-01-19 button names match firmware
2025-01-19 let's use KICAD8_3DMODEL_DIR everywhere
2025-01-27 Removed DCDC enable control
2025-02-03 renders and motor tips
2025-02-07 case model link
2025-02-07 Free via size
2025-07-09 tvs slightly moved left
2025-07-09 squeezed caps
2025-08-14 Kicad 9 save
2025-08-14 Kicad 9 board re-update
2025-08-14 Updated to Kicad 9 standard footprints
2025-08-14 fixed uuids and re-updated board; silk_edge_clearance": "ignore",
2025-08-14 Adjusted Nema23 holes to actual StepperOnline motor (51.4mm x 32mm holes)
2025-08-16 Restored thermal relief settings per pads after 9ad340a2dfbe4c9fc7edf243faff8751587aa3d2
2025-08-16 space things out
2025-08-16 added revision v0.5
2025-08-17 fixed clearances
2025-08-17 Moved 120 resistor for easier insertion. CAN looped through the resistor. Removed some vias.
2025-08-19 Smaller optional i2c resistors
2025-08-21 Removed input ferrite bead
2025-08-24 Better Wire Wound Molded SMD Power Inductor
2025-08-31 Min voltage 12V. DCDC shutdown from gpio via mosfet. Large hysteresis using 3.3V feedback resistor to avoid immediate restart if lower than 12V supply.
2025-09-02 straight slot
2025-09-06 Added TVS3300 footprint
2025-09-06 enabled TVS3300
2025-09-06 big cap - down
2025-09-06 moved debug conn to the right a bit
2025-09-06 separate 100k resistor for ADMT4000 test circuit
2025-09-06 mount holes thermal relief for optional studs
2025-09-06 minor
2025-09-06 pads "excluded form bom"
2025-09-06 parts availability
2025-09-06 relocated tooling holes
2025-09-06 SSL54 schottky
2025-09-06 Unidirectional TVS
2025-09-06 rotations
2025-09-06 removed jlc mark
2025-09-08 SOT-23 PESDCAN
2025-09-08 U2 make dot visible
2025-10-09 corrections and todos
2025-10-09 tuned start voltage ~11.9V 56k 3.3v hysteresis loop
2025-10-09 Remove TVS3300
2025-10-09 Moved D7 higher to not confuse jlc
2025-10-09 connect dcdc shutdown mosfet gate
2025-11-21 Removed R3 to force always enable

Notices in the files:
PCB/StepperServoCAN.kicad_sch:
Licensed under CERN-OHL-S v2
